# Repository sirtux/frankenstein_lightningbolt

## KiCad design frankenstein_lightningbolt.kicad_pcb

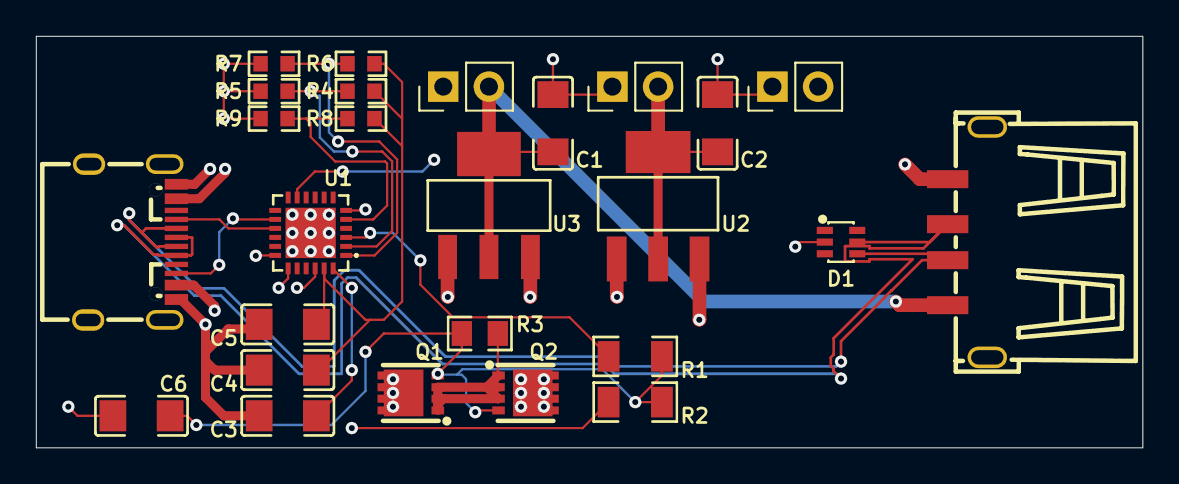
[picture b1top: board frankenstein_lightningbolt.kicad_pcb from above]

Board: 4 copper layers, 61.5 x 22.9 mm, 26 parts (0 on the bottom side), 17 nets.

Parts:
C1, C2: 22uF 25V 1206 RoHS; C1206
C3, C4, C6: 1uF 50V 1206 RoHS; C1206
C5: 100nF 50V 1206 RoHS; C1206
D1: SMF05CT1G; SOT-363_L2.0-W1.3-P0.65-LS2.1-BR
J1: 12V OUT; PinHeader_1x02_P2.54mm_Vertical
J2: 3V3 OUT; PinHeader_1x02_P2.54mm_Vertical
J3: 5V OUT; PinHeader_1x02_P2.54mm_Vertical
Q1, Q2: DMP3013SFV-7; POWERPAK-1212-8_L3.1-W3.1-P0.65-LS3.3-BL
R1: 1KOhms ±1% 1/4W 1206 RoHS; R1206
R2: 10KOhms 1206; R1206
R3: 47KOhms ±1% 1/8W 0805 RoHS; R0805
R4, R6, R8: 5.1k 0603; R0603
R5, R7: 2.4k 0603; R0603
R9: 10k 0603; R0603
U1: CYPD3177-24LQXQ; TQFN-24_L4.0-W4.0-P0.50-TL-EP2.8
U2: AMS1117-3.3; SOT-223-3_L6.5-W3.4-P2.30-LS7.0-BR
U3: AMS1117-5.0; SOT-223_L6.5-W3.5-P2.30-LS7.0-BR
USB1: AF10.0 Aparagraph After the two feet Boundless ir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; USB-A-SMD_JTJ-USB-AF-10.0-023
USBC1: USB3.1C16PFSMT; USB-C-SMD_TYPE-C-USB-17

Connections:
+3V3: C2.1, J2.2, U2.2 (VOUT), U2.4 (VOUT)
+5V: C1.1, J3.2, U3.2 (VOUT), U3.4 (VOUT), USB1.1 (VCC)
/CC1: U1.15 (CC1), USBC1.A5 (CC1)
/CC2: U1.14 (CC2), USBC1.B5 (CC2)
/ISNK_COARSE: R8.2, R9.1, U1.5 (ISNK_COARSE)
/USB+: D1.5, USB1.3 (D+), USBC1.A6 (DP1), USBC1.B6 (DP2)
/USB-: D1.4, USB1.2 (D-), USBC1.A7 (DN1), USBC1.B7 (DN2)
/VBUS_FET_EN: C6.2, Q1.4 (G), Q2.4 (G), R1.1, R2.2, R3.1
/VBUS_MAX: R4.2, R5.1, U1.2 (VBUS_MAX)
/VBUS_MIN: R6.2, R7.1, U1.1 (VBUS_MIN)
/VDDD: C4.2, C5.1, R4.1, R6.1, R8.1, U1.23 (VDDD)
GND: C1.2, C2.2, C3.1, C4.1, C5.2, D1.2, J1.1, J2.1, J3.1, R5.2, R7.2, R9.2, U1.6 (ISNK_FINE), U1.19 (GND), U1.22 (GND), U1.25 (EP), U2.1 (GND), U3.1 (GND), USB1.4 (GND), USB1.6, USBC1.0, USBC1.A1 (GND), USBC1.A12 (GND)
unnamed: Q1.1 (S), Q1.2 (S), Q1.3 (S), Q2.1 (S), Q2.2 (S), Q2.3 (S), R3.2
unnamed: R1.2, U1.3 (VBUS_FET_EN)
unnamed: C3.2, U1.24 (VCCD)
VBUS: C6.1, D1.6, Q1.5 (D), Q1.6 (D), Q1.7 (D), Q1.8 (D), R2.1, U1.18 (VBUS_IN), USBC1.A4 (VBUS), USBC1.A9 (VBUS)
Vdrive: J1.2, Q2.5 (D), Q2.6 (D), Q2.7 (D), Q2.8 (D), U1.11 (VDC_OUT), U2.3 (VIN), U3.3 (VIN)

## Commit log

2023-05-23 Base Repo
2023-05-23 Initial schematic
2023-05-23 Fix Part IDs and missing footprints
2023-05-23 Add GND to usb connectors
2023-05-23 Routing v1
